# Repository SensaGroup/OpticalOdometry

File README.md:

# OpticalOdometry
V 1.2 Optical Odometry for our system 2019.

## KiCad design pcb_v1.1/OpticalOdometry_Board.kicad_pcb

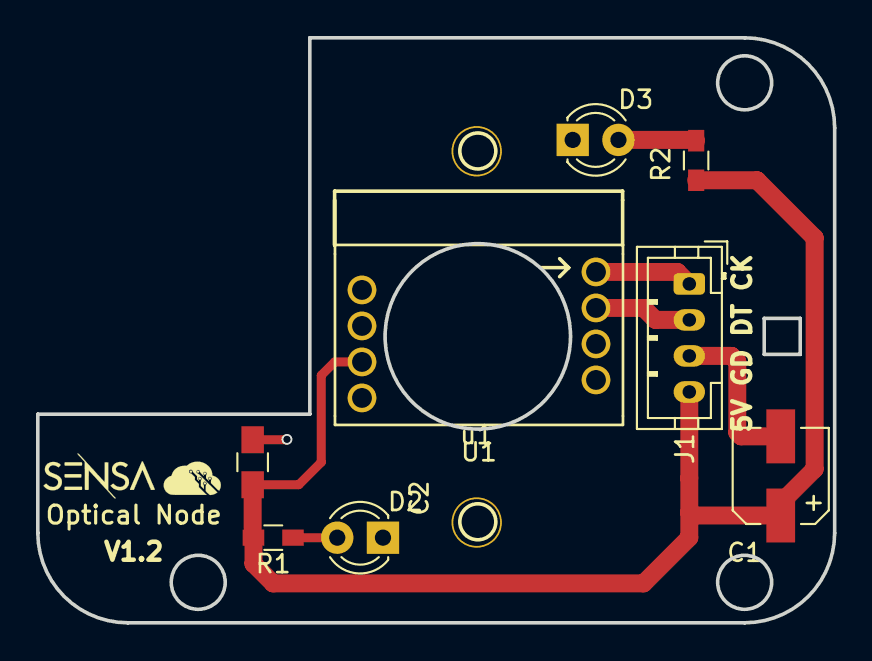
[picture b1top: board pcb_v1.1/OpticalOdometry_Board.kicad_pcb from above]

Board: 2 copper layers, 44.3 x 32.5 mm, 9 parts (0 on the bottom side), 6 nets.

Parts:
C1: 25V 10uf; CP_Elec_5x5.7
C2: 25V 10uf; C_0805_HandSoldering
D2, D3: LED; LED_D3.0mm
J1: Conn_01x04; JST_PH_B4B-PH-K_1x04_P2.00mm_Vertical
R1, R2: 220R; R_0603_HandSoldering
U1: ADNS-2610
u1: Holder

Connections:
GND: C1.2, C2.2, D2.1, D3.1, J1.3, U1.6
unnamed: D2.2, R1.1
unnamed: D3.2, R2.1
unnamed: J1.1, U1.4
unnamed: J1.2, U1.3
VCC: C1.1, C2.1, J1.4, R1.2, R2.2, U1.7

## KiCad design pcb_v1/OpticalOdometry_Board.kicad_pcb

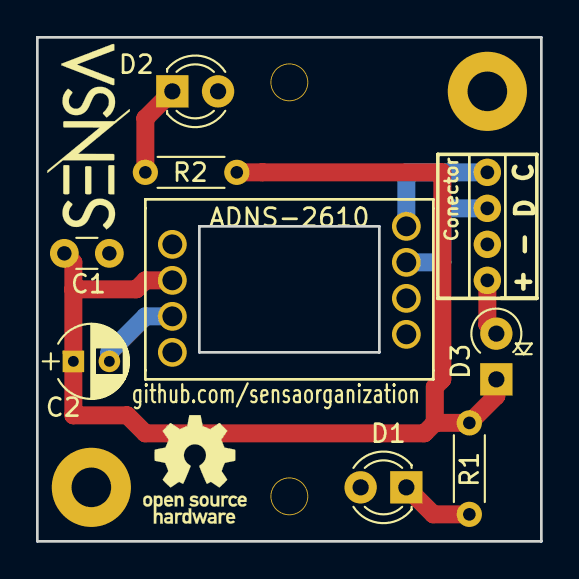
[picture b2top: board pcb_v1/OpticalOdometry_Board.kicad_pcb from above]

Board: 2 copper layers, 28.0 x 28.0 mm, 10 parts (0 on the bottom side), 7 nets.

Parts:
ADNS-2610: u; ADNS-2610
C1: 25V, 10up; C_Disc_D3.0mm_W1.6mm_P2.50mm
C2: 25V, 10up; CP_Radial_D4.0mm_P2.00mm
Conector: Conector; Conection
D1, D2: LED; LED_D3.0mm
D3: D3; D_A-405_P2.54mm_Vertical_KathodeUp
R1, R2: 1000R; R_Axial_DIN0204_L3.6mm_D1.6mm_P5.08mm_Horizontal
\: Mounting_Hole; MountingHole_2.2mm_M2_Pad

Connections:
unnamed: ADNS-2610.6, C1.1, C2.1, D3.1, R1.2, R2.2
unnamed: ADNS-2610.7, C1.2, C2.2, Conector.2, D1.2, D2.2
unnamed: D1.1, R1.1
unnamed: D2.1, R2.1
unnamed: Conector.1, D3.2
unnamed: ADNS-2610.3, Conector.3
unnamed: ADNS-2610.4, Conector.4

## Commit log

2018-05-21 first version of the optical driver board
2018-05-21 Pcb Version_1
2018-05-21 Added logos to the board and the folder
2018-05-21 Added images, plot and main outputs
2018-05-21 Added image
2018-08-23 design fixes
2018-08-30 Added just pcb v1 for release
2018-08-30 Small changes, arranged files into folders, ready to be sent
2018-08-30 README
2018-08-30 normal names for variables
2019-03-13 new version
